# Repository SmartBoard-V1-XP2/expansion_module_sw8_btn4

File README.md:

# Expansion odule : 8-position rotary switch and 4 buttons 

Control Input Module for Smartboard

## Overview
This repository hosts the design and implementation details of a Control Input Module for the smartboard. Incorporating an 8-position rotary switch, 4 buttons, and a single digit 7-segment display, this module is powered by an ATtiny48 microcontroller. It is designed to serve as a versatile control interface for smartboard applications, utilizing two smartboard connectors for enhanced functionality.

## Key Features
- **8-Position rotary Switch and 4 Buttons**: Provides a comprehensive set of inputs for control and selection tasks.
- **Single Digit 7-Segment Display**: Offers visual feedback for settings or values.
- **ATtiny48 Microcontroller**: A compact, low-power microcontroller from Microchip, known for its versatility and efficiency in handling I/O operations, making it ideal for embedded applications.
- **Smartboard Compatibility**: Designed to connect seamlessly with two smartboard connectors, facilitating easy integration with existing systems.
- **Customizable Input Handling**: The ATtiny48 allows for flexible programming to accommodate various input scenarios and application requirements.

### Schematic

*Detailed schematic showing the connections between the ATtiny48, the switch, buttons, and the 7-segment display.*

### Board Design

*A visual representation of the PCB layout, highlighting the placement of the ATtiny48, the input controls, and the display.*

## Programming and Configuration
The ATtiny48 microcontroller can be programmed via the ISP interface, allowing for easy customization of the module's behavior. Users can develop and upload their own firmware to tailor the module's operation for specific applications or to add new features.

## Contributions and Feedback
Contributions to this project are welcome. If you have suggestions for improvement or have developed additional features, please fork the repository, make your changes, and submit a pull request. For any questions or issues, please open an issue in the GitHub repository.

## License
This charger project is licensed under the MIT License with the following terms:

- **Permission to Use**: You are free to use, modify, and distribute this charger design in both private and commercial settings.
- **Attribution Requirement**: While not required, attribution to the original author, Adam Łuczak, is appreciated. This can be done through a citation or a link back to this repository.
- **No Warranty**: This design is provided "as is", without warranty of any kind. Use it at your own risk.
- **Liability**: The author is not liable for any damages or losses that may arise from the use of this design.

For the full terms and conditions, please refer to the MIT License documentation.

## Contact
Should you have any inquiries or suggestions regarding this charger project, please don't hesitate to contact Adam Łuczak at adam.luczak@outlook.com.

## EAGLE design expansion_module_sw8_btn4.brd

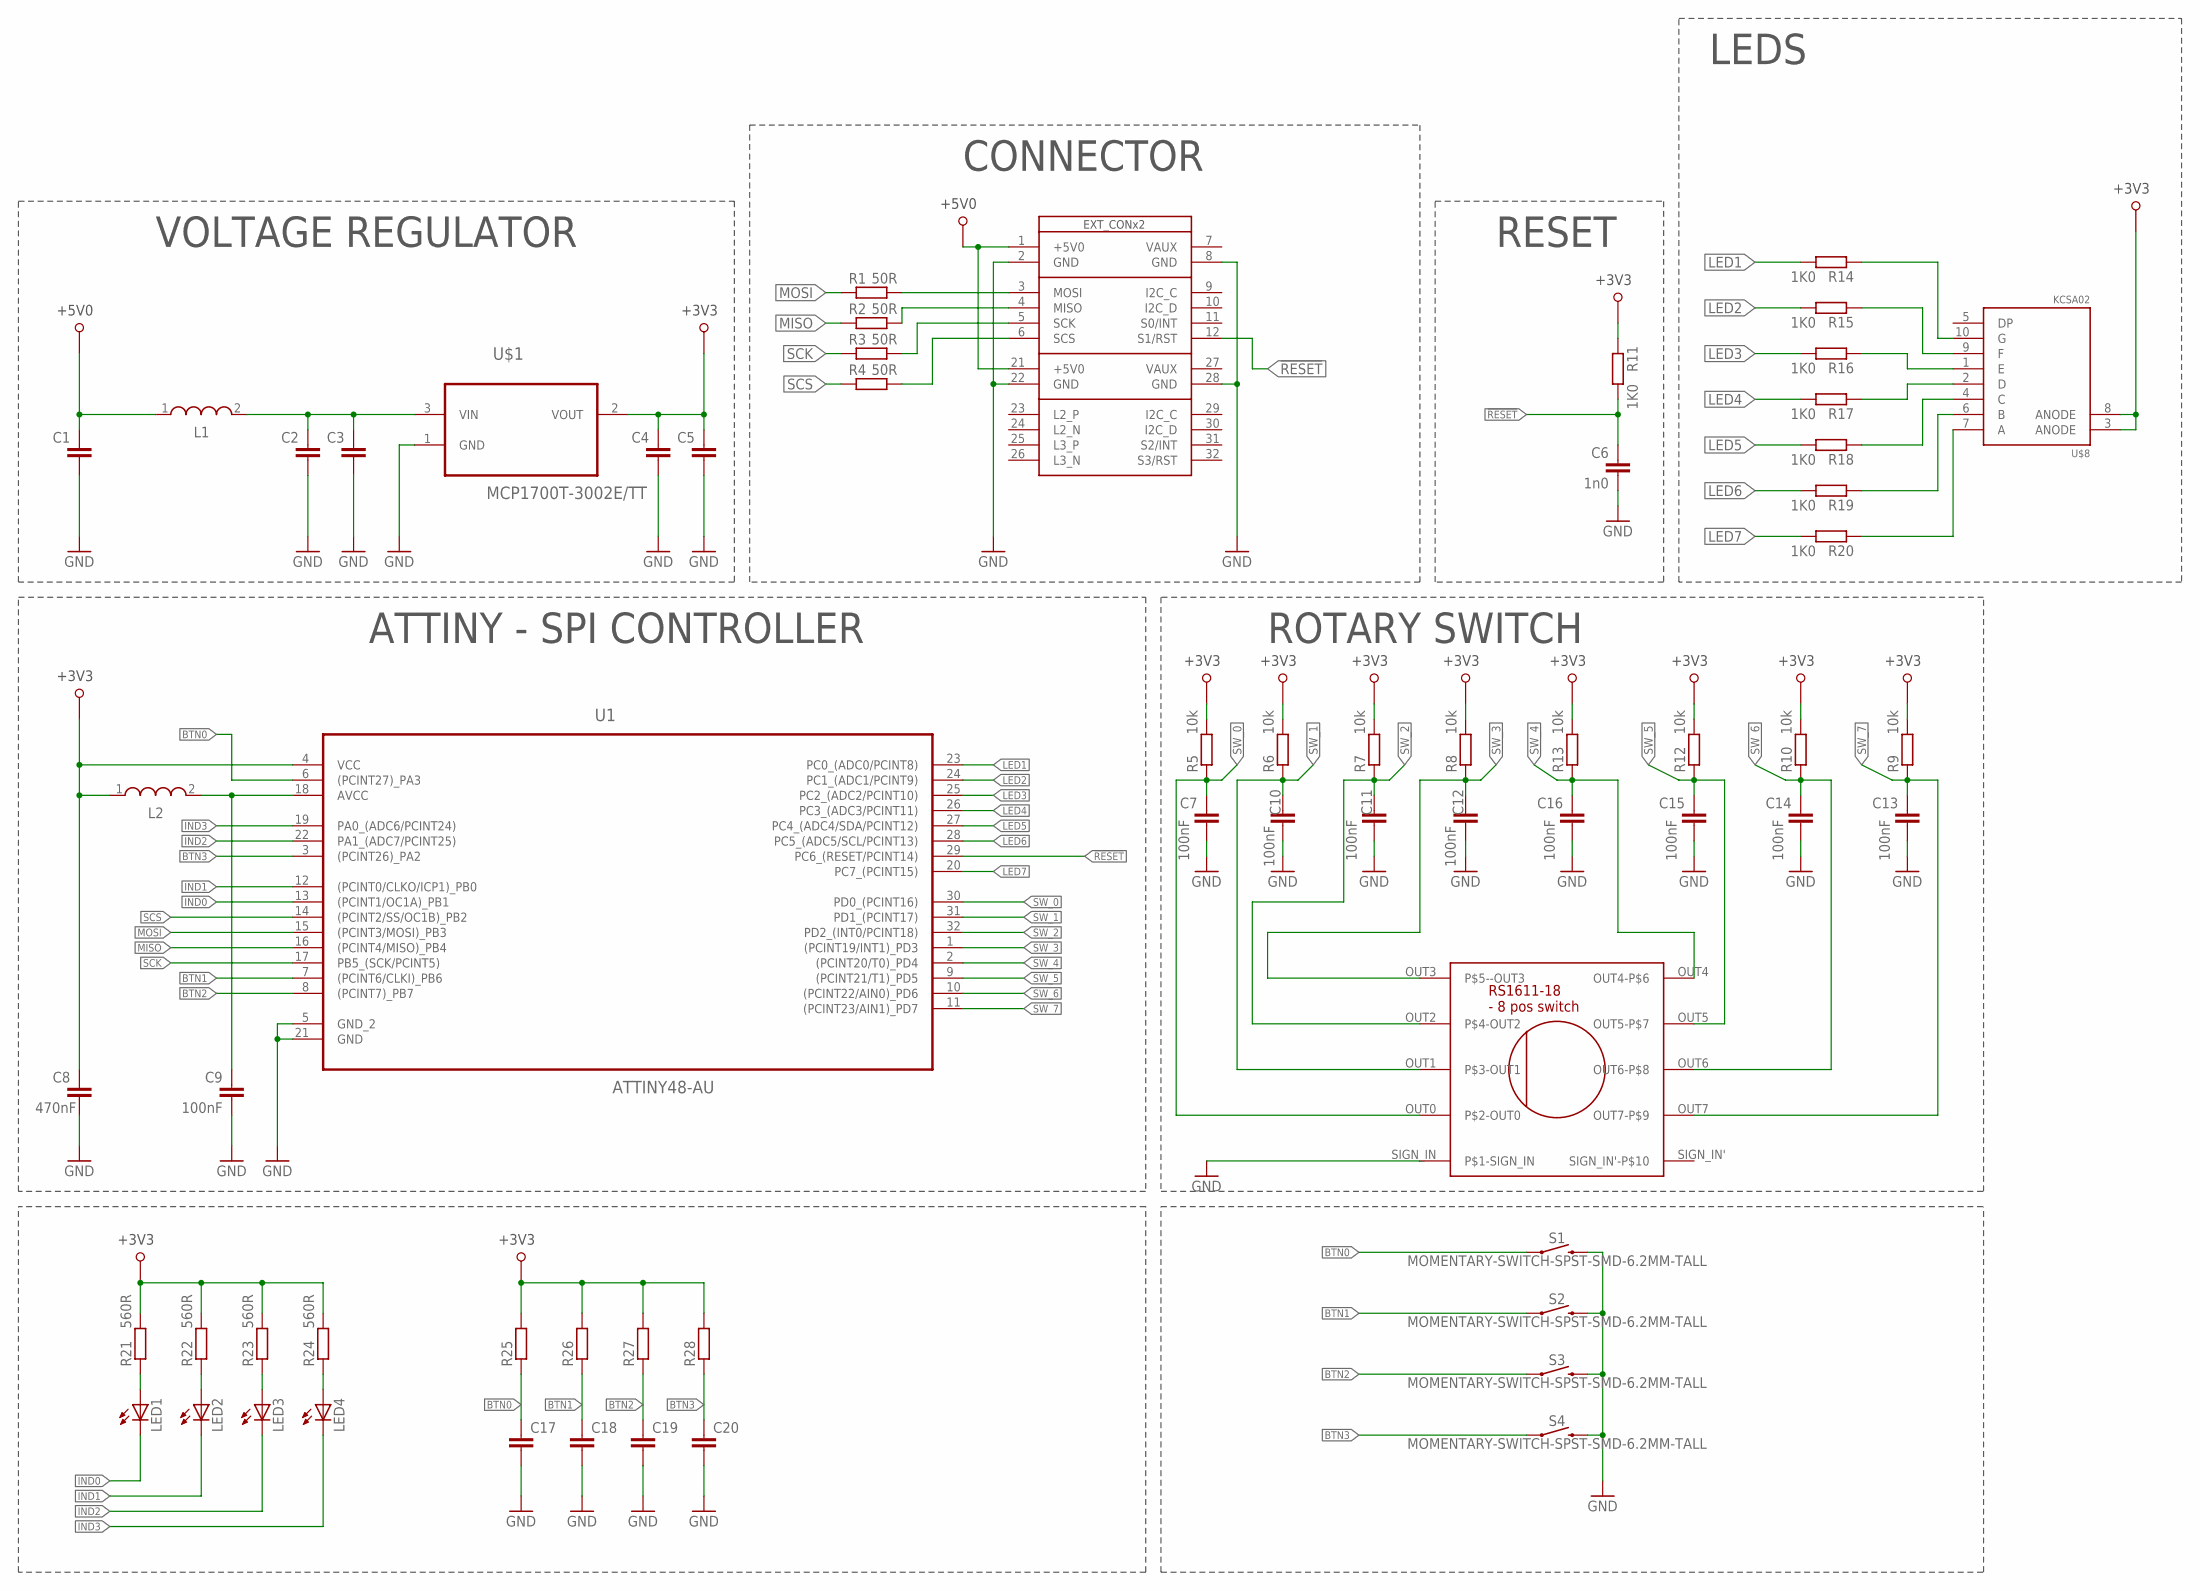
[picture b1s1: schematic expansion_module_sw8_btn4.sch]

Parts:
C1, C2, C3, C4, C5: C-EUC0805; C0805
C6: 1n0; C0805
C7, C9, C10, C11, C12, C13, C14, C15, C16: 100nF; C0805
C8: 470nF; C0805
C17, C18, C19, C20: C-EUC0603K; C0603K
L1: WE-LQ_1210; WE-LQ_M
L2: WE-PMI_0805
LED1, LED2, LED3, LED4: LEDCHIPLED_0805; CHIPLED_0805
R1, R2, R3, R4: 50R; R0805
R5, R6, R7, R8, R9, R10, R12, R13: 10k; R0805
R11, R14, R15, R16, R17, R18, R19, R20: 1K0; R0805
R21, R22, R23, R24: 560R; R0805
R25, R26, R27, R28: R-EU_R0603; R0603
S1, S2, S3, S4: MOMENTARY-SWITCH-SPST-SMD-6.2MM-TALL; TACTILE_SWITCH_SMD_6.2MM_TALL
U1: ATTINY48-AU; QFP80P900X900X120-32N
U$1: MCP1700T-3002E/TT; SOT95P237X112-3N
U$8: KCSA02-109-SMALL; KCSX02-SM
U$20: RS1611-18_ROTARY_SW; RS1611-PACKAGE
U$37: SB_EXT_CON_X2_SPI; SB_EXT_CON_X2_FULL

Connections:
!RESET: C6.2, R11.2, U1.29 (PC6_(RESET/PCINT14)), U$37.12 (S1/RST)
+3V3: C4.2, C5.2, C8.2, L2.1, R5.2, R6.2, R7.2, R8.2, R9.2, R10.2, R11.1, R12.2, R13.2, R21.2, R22.2, R23.2, R24.2, R25.2, R26.2, R27.2, R28.2, U1.4 (VCC), U$1.2 (VOUT), U$8.3 (ANODE), U$8.8 (ANODE)
+5V0: C1.2, L1.1, U$37.1 (+5V0), U$37.21 (+5V0)
BTN0: C17.1, R25.1, S1.A2 (1), U1.6 ((PCINT27)_PA3)
BTN1: C18.1, R26.1, S2.A2 (1), U1.7 ((PCINT6/CLKI)_PB6)
BTN2: C19.1, R27.1, S3.A2 (1), U1.8 ((PCINT7)_PB7)
BTN3: C20.1, R28.1, S4.A2 (1), U1.3 ((PCINT26)_PA2)
GND: C1.1, C2.1, C3.1, C4.1, C5.1, C6.1, C7.1, C8.1, C9.1, C10.1, C11.1, C12.1, C13.1, C14.1, C15.1, C16.1, C17.2, C18.2, C19.2, C20.2, S1.B2 (2), S2.B2 (2), S3.B2 (2), S4.B2 (2), U1.5 (GND_2), U1.21 (GND), U$1.1 (GND), U$20.SIGN_IN (P$1-SIGN_IN), U$37.2 (GND), U$37.8 (GND), U$37.22 (GND), U$37.28 (GND)
IND0: LED1.C, U1.13 ((PCINT1/OC1A)_PB1)
IND1: LED2.C, U1.12 ((PCINT0/CLKO/ICP1)_PB0)
IND2: LED3.C, U1.22 (PA1_(ADC7/PCINT25))
IND3: LED4.C, U1.19 (PA0_(ADC6/PCINT24))
LED1: R14.2, U1.23 (PC0_(ADC0/PCINT8))
LED2: R15.2, U1.24 (PC1_(ADC1/PCINT9))
LED3: R16.2, U1.25 (PC2_(ADC2/PCINT10))
LED4: R17.2, U1.26 (PC3_(ADC3/PCINT11))
LED5: R18.2, U1.27 (PC4_(ADC4/SDA/PCINT12))
LED6: R19.2, U1.28 (PC5_(ADC5/SCL/PCINT13))
LED7: R20.2, U1.20 (PC7_(PCINT15))
MISO: R2.1, U1.16 ((PCINT4/MISO)_PB4)
MOSI: R1.1, U1.15 ((PCINT3/MOSI)_PB3)
unnamed: R1.2, U$37.3 (MOSI)
unnamed: R2.2, U$37.4 (MISO)
unnamed: R3.2, U$37.5 (SCK)
unnamed: R4.2, U$37.6 (SCS)
unnamed: C9.2, L2.2, U1.18 (AVCC)
unnamed: LED1.A, R21.1
unnamed: C2.2, C3.2, L1.2, U$1.3 (VIN)
unnamed: R14.1, U$8.10 (G)
unnamed: R15.1, U$8.9 (F)
unnamed: R16.1, U$8.1 (E)
unnamed: R17.1, U$8.2 (D)
unnamed: R18.1, U$8.4 (C)
unnamed: R19.1, U$8.6 (B)
unnamed: R20.1, U$8.7 (A)
unnamed: LED2.A, R22.1
unnamed: LED3.A, R23.1
unnamed: LED4.A, R24.1
SCK: R3.1, U1.17 (PB5_(SCK/PCINT5))
SCS: R4.1, U1.14 ((PCINT2/SS/OC1B)_PB2)
SW_0: C7.2, R5.1, U1.30 (PD0_(PCINT16)), U$20.OUT0 (P$2-OUT0)
SW_1: C10.2, R6.1, U1.31 (PD1_(PCINT17)), U$20.OUT1 (P$3-OUT1)
SW_2: C11.2, R7.1, U1.32 (PD2_(INT0/PCINT18)), U$20.OUT2 (P$4-OUT2)
SW_3: C12.2, R8.1, U1.1 ((PCINT19/INT1)_PD3), U$20.OUT3 (P$5--OUT3)
SW_4: C16.2, R13.1, U1.2 ((PCINT20/T0)_PD4), U$20.OUT4 (OUT4-P$6)
SW_5: C15.2, R12.1, U1.9 ((PCINT21/T1)_PD5), U$20.OUT5 (OUT5-P$7)
SW_6: C14.2, R10.1, U1.10 ((PCINT22/AIN0)_PD6), U$20.OUT6 (OUT6-P$8)
SW_7: C13.2, R9.1, U1.11 ((PCINT23/AIN1)_PD7), U$20.OUT7 (OUT7-P$9)

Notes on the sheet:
CONNECTOR
VOLTAGE REGULATOR
ATTINY - SPI CONTROLLER
ROTARY SWITCH
RESET
LEDS

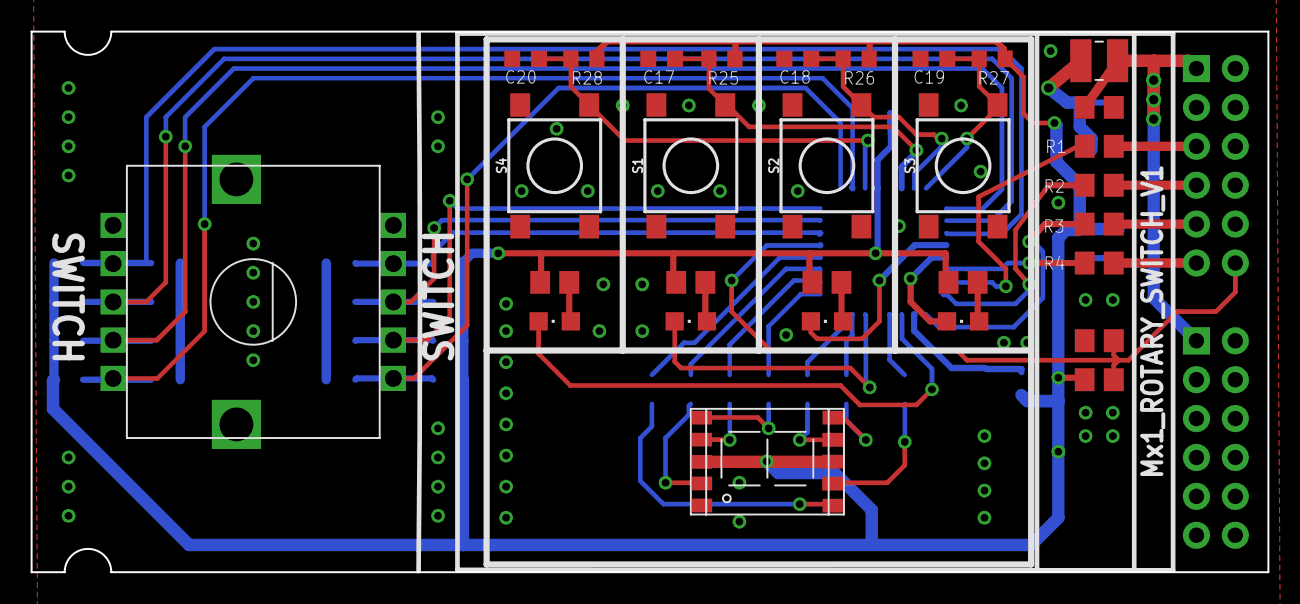
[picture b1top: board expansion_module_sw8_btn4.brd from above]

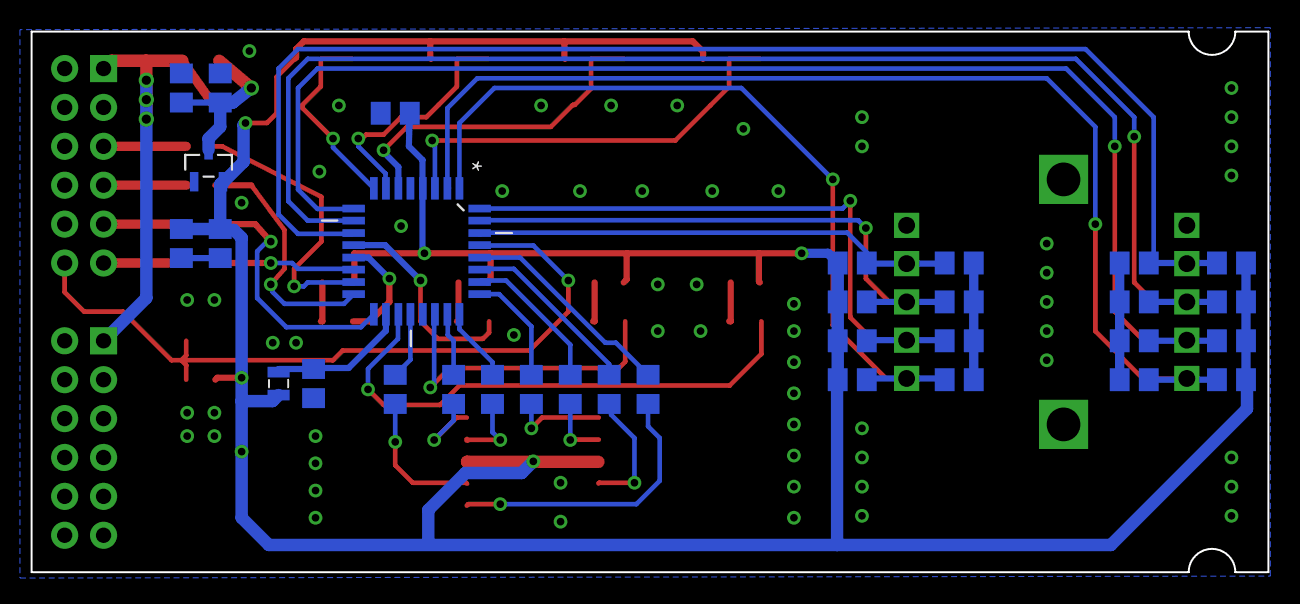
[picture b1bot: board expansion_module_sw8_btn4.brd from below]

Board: 2 copper layers, 80.8 x 35.3 mm, 63 parts (32 on the bottom side), 48 nets.

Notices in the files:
README.md:
License: MIT
parts and their libraries:
EagleLibrary_Wuerth_Elektronik_eiSos_rev: Copyright: Würth Elektronik
SparkFun-Switches: Licensing: Creative Commons ShareAlike 4.0 International - https://creativecommons.org/licenses/by-sa/4.0
